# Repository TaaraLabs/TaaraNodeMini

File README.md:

TaaraNode Mini
==============

Small Arduino/JeeNode compatible microcontroller board with RFM12b radio

[WebSite](https://taaralabs.eu/nm1)

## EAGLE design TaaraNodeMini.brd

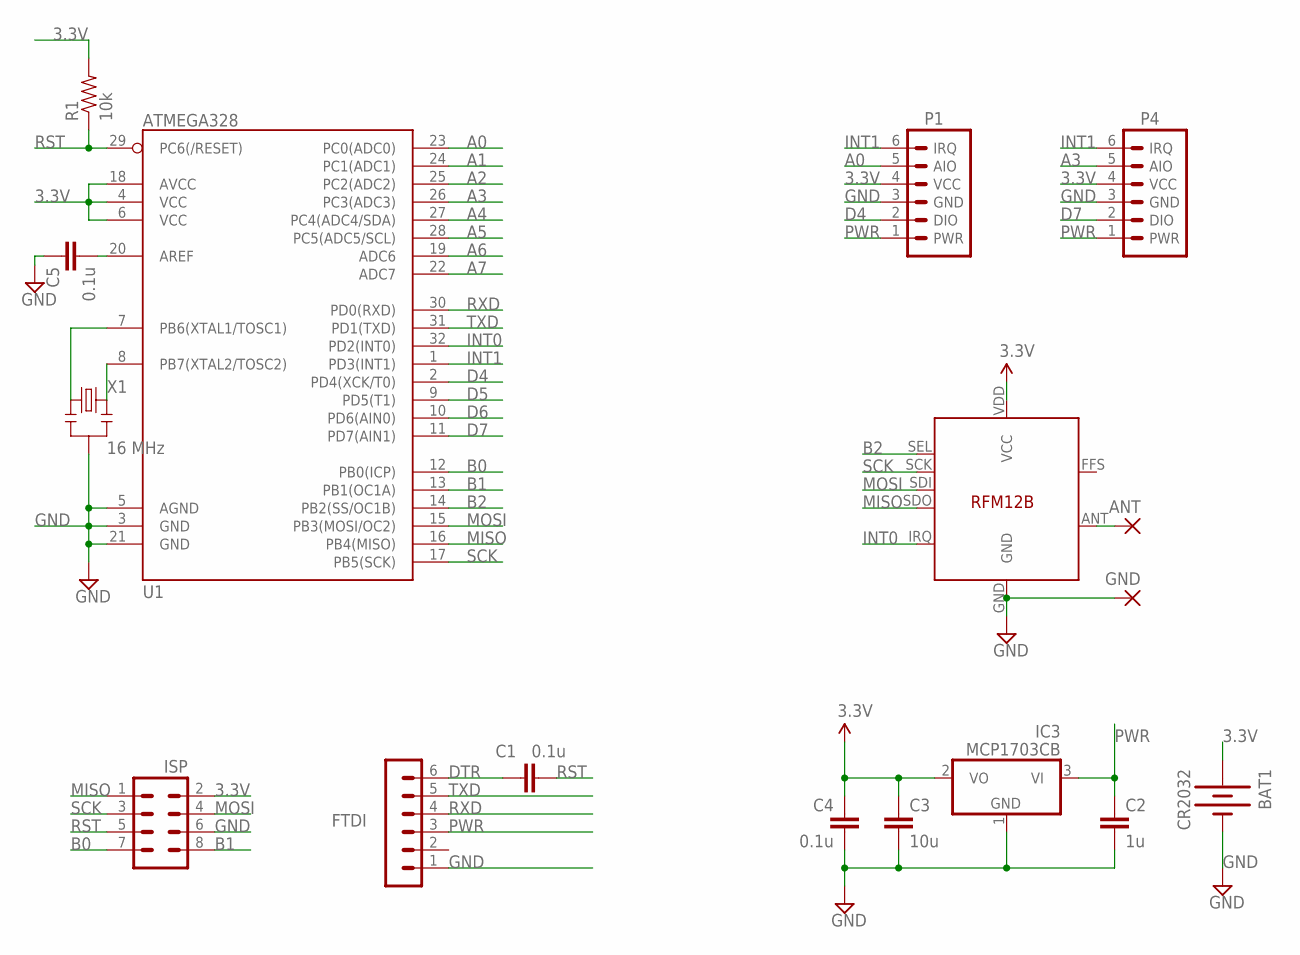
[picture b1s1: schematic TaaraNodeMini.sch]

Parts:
ANT: 1,6/0,8
BAT1: CR2032; BATTCOM_20MM_PTH
C1, C4, C5: 0.1u; 0603-CAP
C2: 1u; 0603-CAP
C3: 10u; 0805
FTDI: FTDI; MA06-1
GND: 1,6/0,8
IC3: MCP1703CB; SOT23
P1, P4: JEEPORT; 1X06_FEMALE_LOCK.010
R1: 10k; 0603-RES
SV7: ISP; MA04-2
U1: ATMEGA328; TQFP32-08
U$1: RFM12B
X1: 16 MHz; RESONATOR-SMD

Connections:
3.3V: BAT1.1 (+), C3.1, C4.1, IC3.2 (VO), P1.4 (VCC), P4.4 (VCC), R1.2, SV7.2, U1.4 (VCC), U1.6 (VCC), U1.18 (AVCC), U$1.VDD (VCC)
A0: P1.5 (AIO), U1.23 (PC0(ADC0))
A1: U1.24 (PC1(ADC1))
A2: U1.25 (PC2(ADC2))
A3: P4.5 (AIO), U1.26 (PC3(ADC3))
A4: U1.27 (PC4(ADC4/SDA))
A5: U1.28 (PC5(ADC5/SCL))
A6: U1.19 (ADC6)
A7: U1.22 (ADC7)
AREF: C5.2, U1.20 (AREF)
B0: SV7.7, U1.12 (PB0(ICP))
B1: SV7.8, U1.13 (PB1(OC1A))
B2: U1.14 (PB2(SS/OC1B)), U$1.SEL
D4: P1.2 (DIO), U1.2 (PD4(XCK/T0))
D5: U1.9 (PD5(T1))
D6: U1.10 (PD6(AIN0))
D7: P4.2 (DIO), U1.11 (PD7(AIN1))
DTR: C1.2, FTDI.6
GND: BAT1.2 (-), C2.2, C3.2, C4.2, C5.1, FTDI.1, GND.1, IC3.1 (GND), P1.3 (GND), P4.3 (GND), SV7.6, U1.3 (GND), U1.5 (AGND), U1.21 (GND), U$1.GND, X1.2
INT0: U1.32 (PD2(INT0)), U$1.IRQ
INT1: P1.6 (IRQ), P4.6 (IRQ), U1.1 (PD3(INT1))
MISO: SV7.1, U1.16 (PB4(MISO)), U$1.SDO
MOSI: SV7.4, U1.15 (PB3(MOSI/OC2)), U$1.SDI
unnamed: U1.7 (PB6(XTAL1/TOSC1)), X1.1
unnamed: ANT.1, U$1.ANT
unnamed: U1.8 (PB7(XTAL2/TOSC2)), X1.3
PWR: C2.1, FTDI.3, IC3.3 (VI), P1.1 (PWR), P4.1 (PWR)
RST: C1.1, R1.1, SV7.5, U1.29 (PC6(/RESET))
RXD: FTDI.4, U1.30 (PD0(RXD))
SCK: SV7.3, U1.17 (PB5(SCK)), U$1.SCK
TXD: FTDI.5, U1.31 (PD1(TXD))

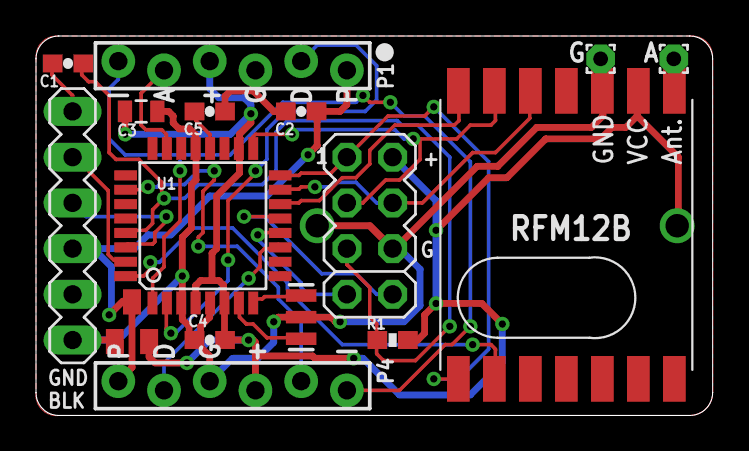
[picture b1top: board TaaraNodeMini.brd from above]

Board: 2 copper layers, 37.6 x 21.1 mm, 18 parts (1 on the bottom side), 23 nets.

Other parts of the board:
U$2: NODEPARAMS

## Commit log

2015-01-22 :lollipop: Added .gitattributes & .gitignore files
2015-01-22 TaaraNodeMini
2015-01-24 TaaraNodeBattery picture replaced
2015-01-24 TaaraNodeMiniLowPower picture added
